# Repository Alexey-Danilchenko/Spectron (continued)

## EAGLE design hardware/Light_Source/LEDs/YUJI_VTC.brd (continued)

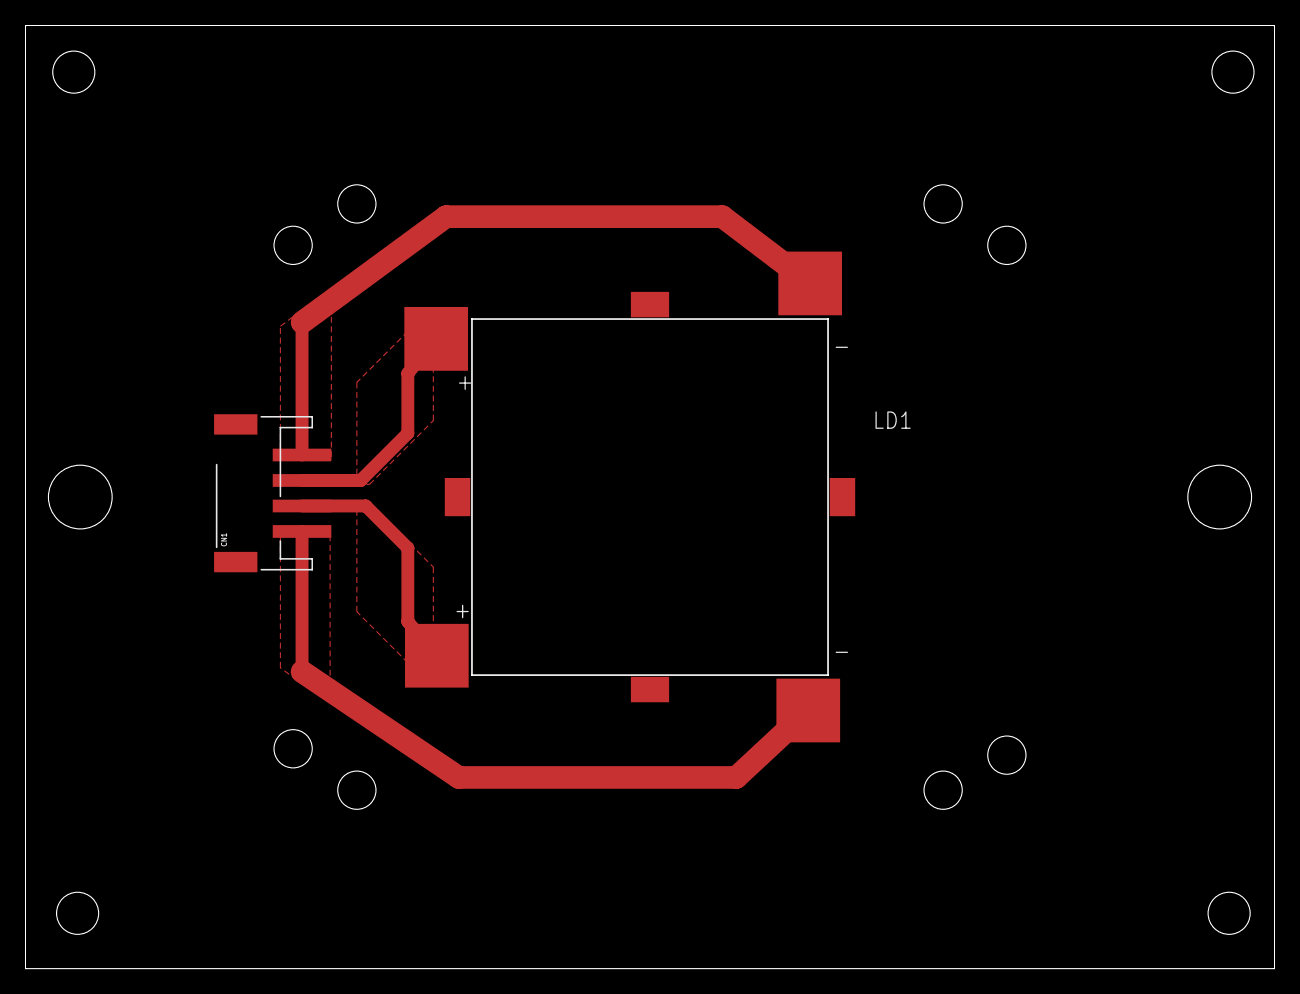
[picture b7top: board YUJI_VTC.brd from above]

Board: 2 copper layers, 98.0 x 74.0 mm, 6 parts (0 on the bottom side), 4 nets.

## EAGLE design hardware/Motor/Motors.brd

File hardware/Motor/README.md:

# Motor controller - programmable to scan of a range of wavelengths

This is the board that is responsible for monochromator automation. The board is capable of driving single stepper motor and receiving input from rotary encoder to help with position verification. The board requires minimum +12V DC power supply to operate. The board is also quite useful as standalone Particle Photon stepper driver.

Board schematic is also [available as standalone PDF](Motors.pdf). Bill of material [is available in Excel format](Motors_BOM.xlsx).

The following are the board layouts available (generated by OSH Park preview):

* Spectron 2 Motors - front and back

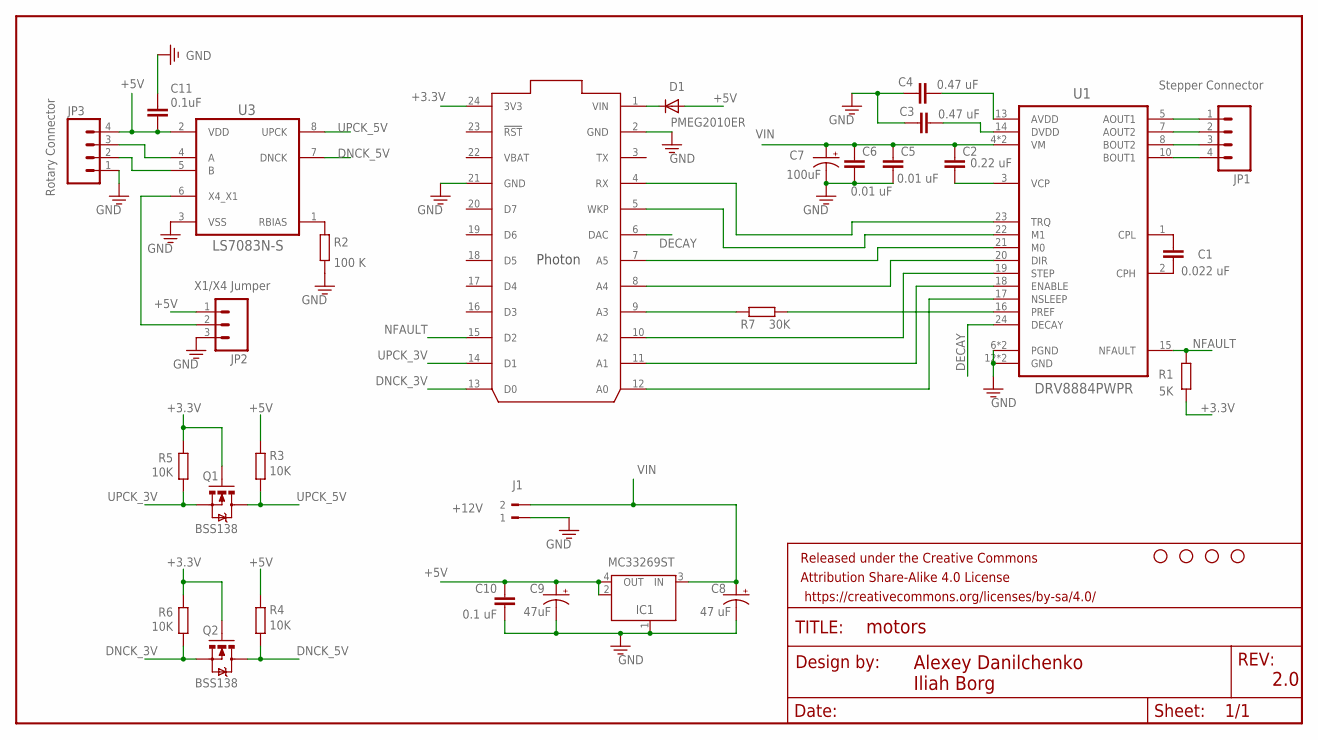
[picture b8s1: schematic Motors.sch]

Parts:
C1: 0.022 uF; C0805
C2: 0.22 uF; C0805
C3, C4: 0.47 uF; C0805
C5, C6: 0.01 uF; C0805
C7: 100uF; CT7343
C8: 47 uF; CT7343
C9: 47uF; CT7343
C10: 0.1 uF; C0805
C11: 0.1uF; C0805
D1: PMEG2010ER; SOD123
FRAME1: FRAME-LETTER; CREATIVE_COMMONS
IC1: MC33269ST; SOT223
J1: +12V; WEIDMULLER_PM5.08_2
JP1: Stepper Connector; 1X04
JP2: X1/X4 Jumper; 1X03
JP3: Rotary Connector; 1X04
Q1, Q2: BSS138; SOT23-3
R1: 5K; R0805
R2: 100 K; R0805
R3, R4, R5, R6: 10K; R0805
R7: 30K; R0805
STANDOFF1, STANDOFF2, STANDOFF3, STANDOFF4: STAND-OFF
U1: DRV8884PWPR; SOP65P640X120-29N
U2: PHOTON_WITH_HEADERS; PHOTON
U3: LS7083N-S; SOIC127P600X175-8N

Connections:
+3.3V: Q1.1 (G), Q2.1 (G), R1.1, R5.1, R6.1, U2.24 (3V3)
+5V: C9.+, C10.1, C11.2, D1.A, IC1.2 (OUT), IC1.4 (OUT), JP2.1, JP3.4, R3.1, R4.1, U3.2 (VDD)
DECAY: U1.24 (DECAY), U2.6 (DAC)
DNCK_3V: Q2.2 (S), R6.2, U2.13 (D0)
DNCK_5V: Q2.3 (D), R4.2, U3.7 (DNCK)
GND: C3.2, C4.2, C5.2, C6.2, C7.-, C8.-, C9.-, C10.2, C11.1, IC1.1 (GND/ADJ), J1.1, JP2.3, JP3.1, R2.2, U1.6 (PGND), U1.9 (PGND), U1.12 (GND), U1.25 (GND), U2.2 (GND), U2.21 (GND), U3.3 (VSS)
unnamed: U1.18 (ENABLE), U2.11 (A1)
unnamed: C2.2, U1.3 (VCP)
unnamed: C1.1, U1.2 (CPH)
unnamed: C1.2, U1.1 (CPL)
unnamed: U1.22 (M1), U2.5 (WKP)
unnamed: U1.17 (NSLEEP), U2.12 (A0)
unnamed: R7.1, U1.16 (PREF)
unnamed: C4.1, U1.13 (AVDD)
unnamed: C3.1, U1.14 (DVDD)
unnamed: D1.C, U2.1 (VIN)
unnamed: U1.19 (STEP), U2.10 (A2)
unnamed: U1.20 (DIR), U2.8 (A4)
unnamed: U1.21 (M0), U2.7 (A5)
unnamed: U1.23 (TRQ), U2.4 (RX)
unnamed: R7.2, U2.9 (A3)
unnamed: R2.1, U3.1 (RBIAS)
unnamed: JP1.1, U1.5 (AOUT1)
unnamed: JP1.2, U1.7 (AOUT2)
unnamed: JP2.2, U3.6 (X4_X1)
unnamed: JP1.3, U1.8 (BOUT2)
unnamed: JP1.4, U1.10 (BOUT1)
NFAULT: R1.2, U1.15 (NFAULT), U2.15 (D2)
ROTARY_A: JP3.3, U3.4 (A)
ROTARY_B: JP3.2, U3.5 (B)
UPCK_3V: Q1.2 (S), R5.2, U2.14 (D1)
UPCK_5V: Q1.3 (D), R3.2, U3.8 (UPCK)
VBAT: U2.22 (VBAT)
VIN: C2.1, C5.1, C6.1, C7.+, C8.+, IC1.3 (IN), J1.2, U1.4 (VM), U1.11 (VM)

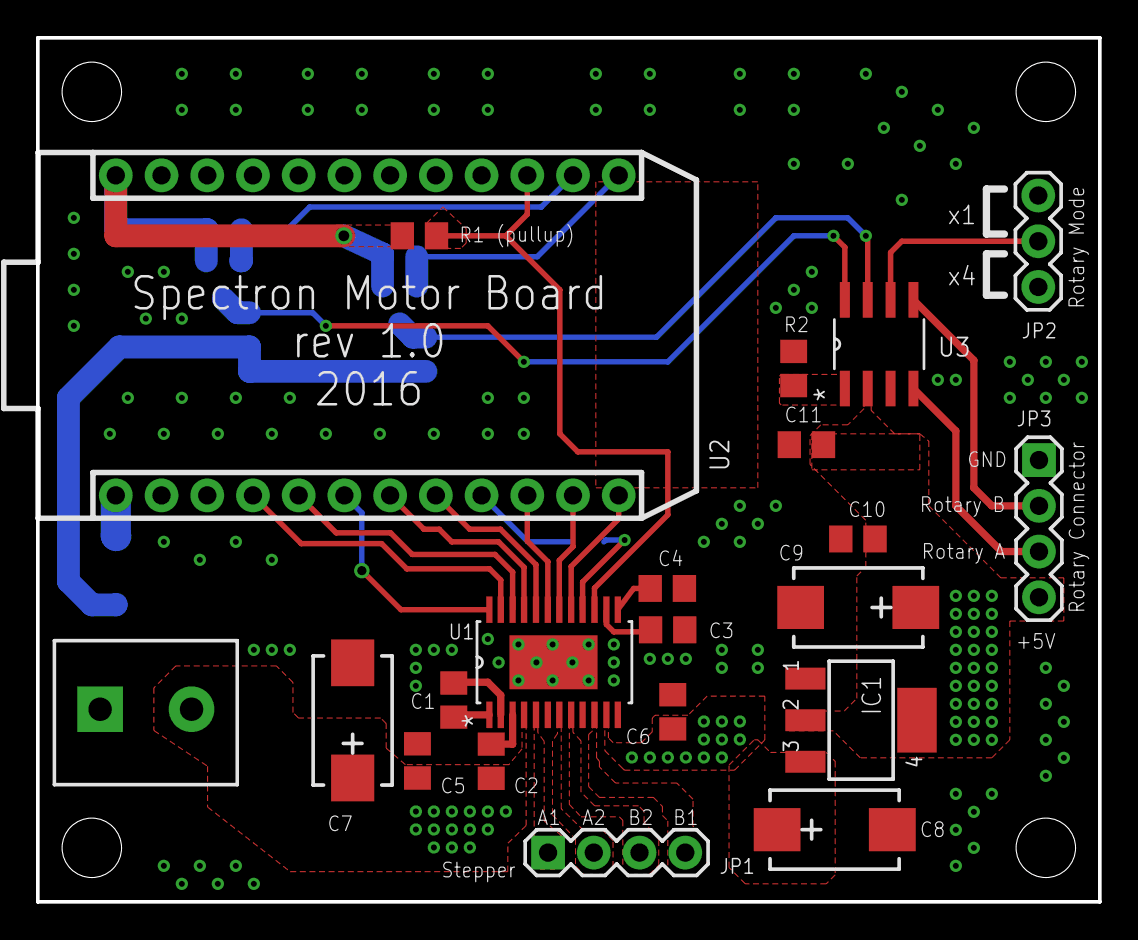
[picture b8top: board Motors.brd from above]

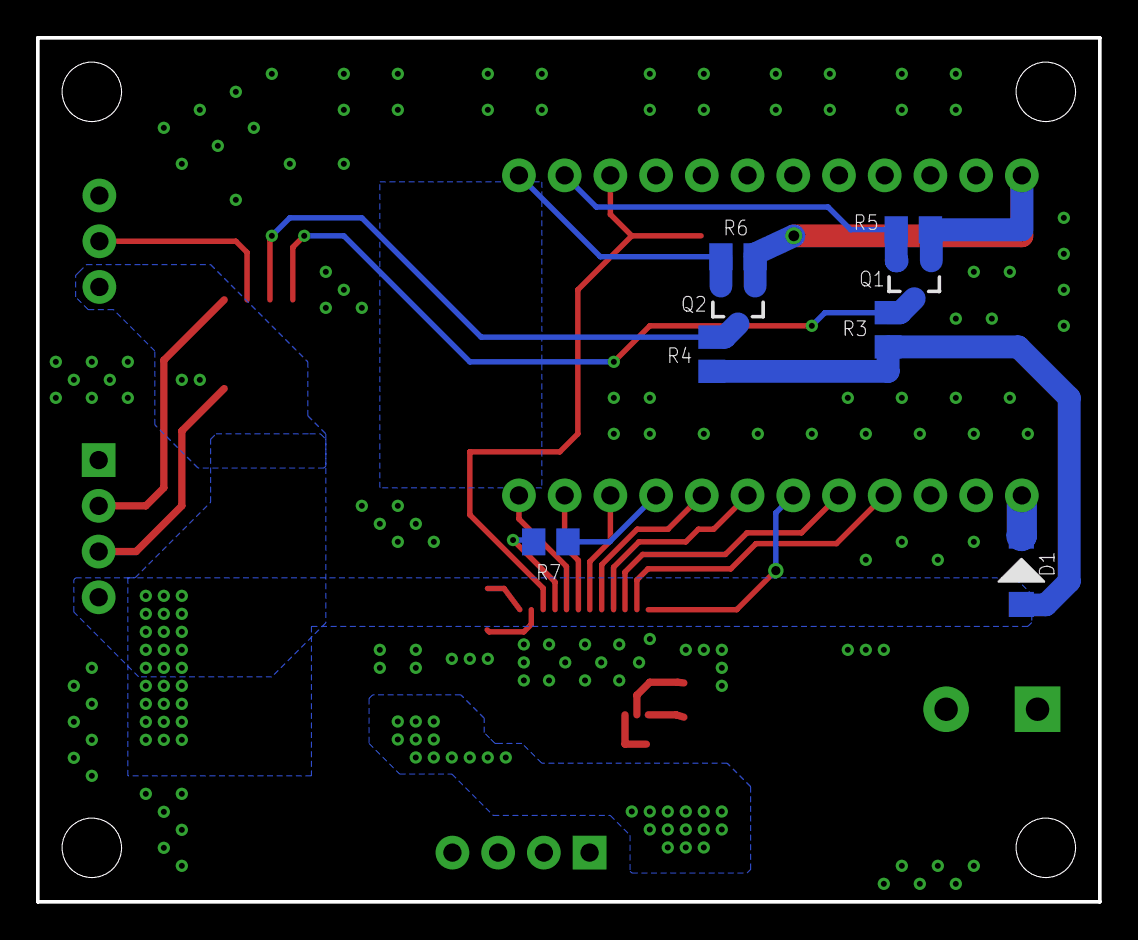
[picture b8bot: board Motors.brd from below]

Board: 2 copper layers, 59.0 x 48.0 mm, 34 parts (8 on the bottom side), 33 nets.

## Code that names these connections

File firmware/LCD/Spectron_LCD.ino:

/*
 *  Spectron_LCD.ino - Demo application of the Spectron board capabilities  
 *                     with Adafruit ILI9340 TFT screen displaying measured 
 *                     spectrum. This is not actively maintained.
 *
 *  Copyright 2015-2017 Alexey Danilchenko
 *
 *  This program is free software; you can redistribute it and/or modify
 *  it under the terms of the GNU General Public License as published by
 *  the Free Software Foundation; either version 3, or (at your option)
 *  any later version with ADDITION (see below).
 *
 *  This program is distributed in the hope that it will be useful,
 *  but WITHOUT ANY WARRANTY; without even the implied warranty of
 *  MERCHANTABILITY or FITNESS FOR A PARTICULAR PURPOSE.  See the
 *  GNU General Public License for more details.

 *  You should have received a copy of the GNU General Public License
 *  along with this program; if not, write to the Free Software
 *  Foundation, 51 Franklin Street - Fifth Floor, Boston,
 *  MA 02110-1301, USA.
 */

SYSTEM_MODE(MANUAL);

#include "C12666MA.h"
#include "Adafruit_ILI9340.h"

#define ADC_REF_SEL_1  A1
#define ADC_REF_SEL_2  A0
#define ADC_CNV        DAC
#define SPI_SS_1       WKP
#define D_PWM          RX
#define SPI_SS_2       A2
#define SPI_MOSI       A5
#define SPI_MISO       A4
#define SPI_SCK        A3
#define SDA            D0
#define SCL            D1

#define TRG_IN         A2   // extrenal trigger button
#define TRG_FLASH      TX
#define TRG_CAMERA     D2

#define TRG_3V         D3
#define EOS_3V         D4
#define CLK_3V         D5
#define ST_3V          D6
#define GAIN_3V        D7

#define LCD_DC        SDA
#define LCD_RESET     SCL
#define LCD_SD_CS     SPI_SS_2
#define LCD_CS        SPI_SS_1
#define LCD_MOSI      SPI_MOSI
#define LCD_MISO      SPI_MISO
#define LCD_SCK       SPI_SCK
#define LCD_BACKLIGHT D_PWM

#define INACTIVE_DELAY_MS 120000

// calibration data for my sensor 15F00163
const float CALIBRATION_15F00163[] =
    {323.3668711, 2.384682045, -5.995865297E-4, -8.602293347E-6, 1.840343099E-8, -1.424592223E-11};

// spectrometer object - can be only one per application
C12666MA spec(TRG_3V,
              EOS_3V,
              GAIN_3V,
              CLK_3V,
              ST_3V,
              TRG_CAMERA,
              ADC_REF_SEL_1,
              ADC_REF_SEL_2,
              ADC_CNV,
              CALIBRATION_15F00163);

// TFT screen object
Adafruit_ILI9340 tft(LCD_SD_CS,
                     LCD_DC,
                     LCD_RESET);

// Wavelength indexes for screen 400,450,500,550,600,650,700,750
#define WV_LABELS      10
#define WV_LABEL_START 350
#define WV_LABEL_STEP  50
uint16_t wvLabelIndex[WV_LABELS];

// indicator if black was measured
bool blackMeasured = true;

// last active time
unsigned long lastActive = 0;

// draw the main screen
void drawScreen()
{
    tft.3Init();
    tft.fillScreen(ILI9340_BLACK);
    tft.setRotation(3);    // orientation landscape

    // draw header
    tft.setCursor(0, 0);
    tft.setTextColor(ILI9340_WHITE);
    tft.setTextSize(1);
    tft.print("Peak: ");
    tft.print(spec.getPeakWavelength(), 2);
    tft.print("nm    Max: ");
    tft.print(spec.getPeakValue());
    tft.print("    Black: ");
    tft.print(spec.getMaxBlack());

    // draw axis
    uint16_t g_x = 0, g_y = 10, g_w = 320, g_h = 220;
    uint16_t color = ILI9340_WHITE;
    tft.drawFastHLine(0, g_y+g_h, g_w, color);
    uint16_t lblWavelength = WV_LABEL_START;
    for (int i=0; i<WV_LABELS; i++)
    {
        if (wvLabelIndex[i] == SPEC_PIXELS)
            break;
        uint16_t l_x = g_x + (wvLabelIndex[i] * g_w / SPEC_PIXELS);
        tft.drawFastVLine(l_x, g_y+g_h-1, 3, color);
        tft.setCursor(l_x - 8, g_y+g_h+2);
        tft.print(lblWavelength);
        lblWavelength += WV_LABEL_STEP;
    }

    // draw the maxvoltage
    // draw spectrum
    if (spec.hasMeasuredData())
    {
        uint16_t x0 = g_x;
        uint16_t y0 = g_y + g_h - (((uint32_t)g_h*spec.getMeasurement(0) + 16383) /16384);
        for (int i=1; i<SPEC_PIXELS; i++)
        {
            uint16_t x1 = g_x + ((i * g_w + SPEC_PIXELS - 1) / SPEC_PIXELS);
            uint16_t y1 = g_y + g_h - (((uint32_t)g_h*spec.getMeasurement(i) + 16383) /16384);
            tft.drawLine(x0, y0, x1, y1, ILI9340_YELLOW);
            x0 = x1;
            y0 = y1;
        }
    }
    else if (!blackMeasured)
    {
        tft.setTextSize(2);
        tft.setCursor(g_x, g_y + (g_h>>1)- 32);
        tft.setTextColor(ILI9340_RED);
        tft.println("    Cover the sensor and");
        tft.println("  trigger black reference");
        tft.println("       measurement");
    }
}

// main firmware initialisation
void setup()
{
    pinMode(LCD_BACKLIGHT, OUTPUT);
    pinMode(LCD_CS,        OUTPUT);
    pinMode(LCD_SD_CS,     OUTPUT);
    pinMode(LCD_DC,        OUTPUT);
    pinMode(LCD_RESET,     OUTPUT);

    pinMode(TRG_IN,     INPUT_PULLUP);
    pinMode(TRG_CAMERA, OUTPUT);
    pinMode(TRG_FLASH,  OUTPUT);

    // reset everything
    pinResetFast(LCD_CS);
    pinResetFast(LCD_SD_CS);
    pinResetFast(LCD_DC);
    pinResetFast(LCD_RESET);


    // initialise spectrometer
    spec.begin();
    spec.setIntTime(500);   // 0.5s to start with
    spec.setAdcReference(ADC_4V);

    // get the wavelength label indexes
    uint16_t idx = 0;
    for (int i=0; i<WV_LABELS; i++)
    {
        uint16_t lblWavelength = WV_LABEL_START + (i * WV_LABEL_STEP);
        while (idx < SPEC_PIXELS &&
               lblWavelength > spec.getWavelength(idx))
               ++idx;
        if (idx < SPEC_PIXELS)
            wvLabelIndex[i] = idx;
        else
            wvLabelIndex[i] = SPEC_PIXELS;
    }

    // enable TFT backlight
    pinSetFast(LCD_BACKLIGHT);
    tft.begin();

    // paint the screen
    drawScreen();

    lastActive = millis();
}

// Main event loop:
//     - Wait for trigger button press
//     - Start spectometer measurement and trigger camera/flash
//     - Display the results on TFT
//     - Store results on SD card
void loop(void)
{
    // poll the trigger button
    if (pinReadFast(TRG_IN) == LOW)
    {
        // debounce check
        delay(100);
        if (pinReadFast(TRG_IN) == LOW)
        {
            pinSetFast(LCD_BACKLIGHT);
            lastActive = millis();
            
            // initiate measurement
            spec.takeMeasurement();

            // paint the screen
            drawScreen();
        }
    }

    // check for inactivity
    if ((millis() - lastActive) > INACTIVE_DELAY_MS)
        pinResetFast(LCD_BACKLIGHT);

    // call for Spark process for manual system mode
    if (Particle.connected())
        Particle.process();
    else
        Particle.connect();
 }

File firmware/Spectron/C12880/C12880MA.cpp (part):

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#define SPEC_PIXELS  288

// standard SPI pins
#define SPI_MOSI    A5
#define SPI_MISO    A4
#define SPI_SCK     A3

//
// State flow with single read integration cycle:
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#define ST_LEAD_TICKS        7            // ticks after ST goes high (on falling CLK) when integration really starts
#define READ_TICKS           ((87 + SPEC_PIXELS)*TICKS_PER_PIXEL)
#define TRG_CYCLES           (SPEC_PIXELS + 88)     // spec pixels + 88 cycles after ST goes low
#define EXT_TRG_HIGH_TICKS   uSecToTicks(1000)      // duration of ext TRG pin high signal - 1mSec

// Integration ticks - change as needed
static uint32_t INTEG_TICKS = MIN_INTEG_TIME_TICKS;
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static uint32_t              specCounter = 0;          // tick counter
static uint32_t              specCLK = 0;              // current clock pin state
static uint32_t              specST = 0;               // current ST pin state
static volatile uint32_t     extTrigger = 0;           // current trigger pin state
static volatile uint32_t     specTRGCounter = 0;       // spec TRG cycles counter
static volatile uint32_t     extTRGCounter = 0;        // ext TRG cycles counter
static volatile uint16_t     specReadCycleCounter = 0; // reading cycles counter
static uint32_t*             specData = 0;             // pointer to current data for ADC reads
static uint16_t*             specDataCounter = 0;      // pointer to current data for ADC reads counter
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#define CR1_CLEAR_MASK   ((uint16_t)0x3040)

// initialise ADC (AD7980) and setup SPI
inline void startADC(uint8_t adc_cnv_pin)
{
    // disable whatever else might have SPI enabled via HAL
    SPI.end();
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    HAL_Pin_Mode(MOSI, AF_OUTPUT_PUSHPULL);

    // Ensure that there is no glitch on SS pin
    PIN_MAP[adc_cnv_pin].gpio_peripheral->BSRRL = PIN_MAP[adc_cnv_pin].gpio_pin;
    HAL_Pin_Mode(adc_cnv_pin, OUTPUT);

    // Get the SPIx CR1 value */
    uint16_t tmpreg = SPI_BASE->CR1;
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
// Function to perform reading ADC7980.
// This does up to two accumulated reads of the ADC
// where the state of the TRG pin is checked following
// the second ADC conversion completion
inline void readADC(uint32_t* data, uint16_t* dataCounts)
{
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// --------------------------------------------------
//   Timer and spectrometer clock handling routines
// --------------------------------------------------
// TRG pin handling interrupt
void spectroTRGInterrupt(void)
{
    if ((EXTI->PR & specPinTRG) && (EXTI->IMR & specPinTRG))
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    TIM_ITConfig(TIM7, TIM_IT_Update, ENABLE);
    TIM_Cmd(TIM7, ENABLE);

    // setup spec TRG pin interrupts
    uint8_t trgPortNumber = 0;  // port A by default

    // clear pending EXTI interrupt flag for the TRG pin
    EXTI->PR = specPinTRG;

    // set the port number
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    else if (specPinTRG_Info->gpio_peripheral == GPIOD)
        trgPortNumber = 3;

    // connect EXTI Line to TRG pin
    SYSCFG_EXTILineConfig(trgPortNumber, specPinTRG_Info->gpio_pin_source);

    // enable TRG pin interrupt
    EXTI->IMR  |= specPinTRG;    // enable interrupt
    EXTI->RTSR |= specPinTRG;    // set raising edge

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    // disable timer peripheral
    TIM_DeInit(TIM7);

    // disable TRG pin interrupts
    EXTI->PR = specPinTRG;       // clear pending
    EXTI->IMR  &= ~specPinTRG;   // mask interrupt
    EXTI->RTSR &= ~specPinTRG;   // clear raising edge

    // disable NVIC IRQ line if it is not shared
    if (sysIrqHandler == 0)
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
    // Setup pins
    pinMode(adc_cnv_,  OUTPUT);
    pinMode(SPI_MOSI,  OUTPUT);
    pinMode(SPI_MISO,  INPUT);
    pinMode(SPI_SCK,   OUTPUT);
    pinMode(spec_eos_, INPUT);
    pinMode(spec_trg_, INPUT);
    pinMode(spec_st_,  OUTPUT);
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
    // reset everything
    pinResetFast(adc_cnv_);
    pinResetFast(SPI_MOSI);
    pinResetFast(SPI_SCK);
    pinResetFast(spec_st_);
    pinResetFast(spec_clk_);
    if (ext_trg_ != NO_PIN)
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    if (ext_trg_ls_ != NO_PIN)
        pinResetFast(ext_trg_ls_);

    // Attach update interrupt for TIM7 and TRG pin
    // HAL version of this would be
    //   attachSystemInterrupt(SysInterrupt_TIM7_IRQ, spectroClockInterrupt);
    //   attachInterrupt(spec_trg_, spectroTRGInterrupt, RAISING, 1);
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    int is = __get_PRIMASK();
	__disable_irq();

    // store the system interrupt if TRG pin ISR is shared across several pins
    if (GPIO_IRQn[trgPinSource] == EXTI9_5_IRQn ||
        GPIO_IRQn[trgPinSource] == EXTI15_10_IRQn)
        sysIrqHandler = (EXT_IRQ_Handler)isrs[trgISRIndex];

    // override TIM7 and TRG pin interrupts
    isrs[TIM7Index]   = (uint32_t)spectroClockInterrupt;
    isrs[trgISRIndex] = (uint32_t)spectroTRGInterrupt;

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        dataCounts[i] = 0;
    }

    // initialise light trigger pin if triggering is enabled
    if (ext_trg_ls_ != NO_PIN && doLightTriggering)
    {
        STM32_Pin_Info* PIN_MAP = HAL_Pin_Map();
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
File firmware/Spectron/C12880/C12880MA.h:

/*
 *  C12880MA.h - Hamamatsu C12880MA driver for Spectron board.
 *
 *  Copyright 2017-2020 Alexey Danilchenko, Iliah Borg
 *
 *  This program is free software; you can redistribute it and/or modify
 *  it under the terms of the GNU General Public License as published by
 *  the Free Software Foundation; either version 3, or (at your option)
 *  any later version with ADDITION (see below).
 *
 *  This program is distributed in the hope that it will be useful,
 *  but WITHOUT ANY WARRANTY; without even the implied warranty of
 *  MERCHANTABILITY or FITNESS FOR A PARTICULAR PURPOSE.  See the
 *  GNU General Public License for more details.

 *  You should have received a copy of the GNU General Public License
 *  along with this program; if not, write to the Free Software
 *  Foundation, 51 Franklin Street - Fifth Floor, Boston,
 *  MA 02110-1301, USA.
 */

#if !defined(_C12880MA_H_)
#define _C12880MA_H_

#include "application.h"
#include "Spectrometer.h"

// Spectrometer class
//
// This class uses TIM7 timer interrupt as well as SPI so it affects their
// configuration when used
//
class C12880MA: public CSpectrometer  {
private:
    // pin definitions - ADC assumes use of the standard SPI pins
    uint8_t adc_cnv_, spec_eos_, spec_trg_, spec_clk_, spec_st_, ext_trg_, ext_trg_ls_;

protected:
    // --------------------------------------------------------------------------
    //  Virtual methods - hardware specific implementations for Hamamatsu C12880
    // --------------------------------------------------------------------------

    // This is the main method that should be overriden by specific spectrometer
    // implementation. It should implement hardware specific initialisation, reading 
    // loop and termination.
    void readSpectrometer(double measTimeUs, 
                          bool doExtTriggering, 
                          bool doLightTriggering) override;

    // Hardware specific sensor constraints - sets data variable for a specific sensor
    // constraint (pointer is expected to point to a variable of correct datatype for 
    // that constraint)
    bool getSensorConstraint(sensor_constraint_t sensConstraint, void* data) override;

    // Hardware specific sets integration time in microseconds for a single
    // measurement cycle.
    //
    // NOTE: if not within sensor allowed boundaries then it will be set to
    //       closest minimum or maximum allowed value
    // NOTE: internally time is measured in clock cycles so real integration
    //       time will be aligned to the clock cycle boundaries
    void setIntTimeInternal(double timeUs, bool saveState = false) override;

    // Hardware specific sets the external trigger to measurement delay time.
    // This defines time interval in uSec that offsets external trigger from 
    // the measurement. I.e. external trigger is raised and after this delay 
    // the integration and measurement starts.
    //
    // Specifying -1 as  delay will disable the external trigger
    void setExtTrgMeasDelayInternal(double delayUs, bool saveState = false) override;

public:

    // Constructor/destructor
    // Parameters:
    //     spec_eos      - C12880MA EOS receving pin
    //     spec_trg      - C12880MA TRG controlling pin
    //     spec_clk      - C12880MA CLK clock pin
    //     spec_st       - C12880MA ST start pin
    //     adc_ref_sel1  - ADC voltage reference selection pin 1
    //     adc_ref_sel2  - ADC voltage reference selection pin 2
    //     adc_cnv       - ADC conversion pin (essentially SPI selection pin for ADC SPI intreface)
    //     ext_trg       - optional trigger pin for capture device (setting HIGH triggers external device)
    //     ext_trg_ls    - optional trigger pin for lightsource (setting HIGH triggers light source)
    //     wvCalibration - factory wavelength calibration factors (array of 6 doubles from Hamamatsu test sheet)
    //     baseEEPROM    - base address to srore the spectrometer settings in EEPROM (-1 if not used)
    C12880MA(uint8_t spec_eos, uint8_t spec_trg, uint8_t spec_clk, uint8_t spec_st,
             uint8_t adc_ref_sel1, uint8_t adc_ref_sel2, uint8_t adc_cnv,
             uint8_t ext_trg, uint8_t ext_trg_ls, 
             const double *wvCalibration, const int baseEEPROM = 0);
    ~C12880MA();

    // Initialise known pins. Specific hardware implementations typically will
    // have their own implementations of this initialising spectrometer specific
    // pins.
    bool begin();

    // --------------------------------------------------------------------------
    //  Virtual methods - hardware specific implementations for Hamamatsu C12666
    // --------------------------------------------------------------------------

    // Return trigger measurement delay in specified units
    double getExtTrgMeasDelay(time_units_t units = T_USEC) override;
    
    // Return integration time in specified units
    double getIntTime(time_units_t units = T_USEC) override;
};

#endif

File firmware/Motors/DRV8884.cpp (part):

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//
#define  TIMER_PRESCALER     599       // for basic timers at 60MHz it gives 10us timer unit counter
#define  TIMER_UNITS_PER_SEC 100000UL  // number of timer units per sec for the above prescaler
#define  MIN_TIMER_PERIOD    10        // min timer tick - in above 10us units it will trigger every 0.1ms
#define  MAX_TIMER_PERIOD    50000     // max timer tick - in above 10us units it will trigger every 500ms
uint32_t TIMER_PERIOD_CNT =  1000;     // in above 10us units it will trigger every 10ms

// State machine
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#endif
                 )
{
    pinNfault_  = nfault;
    pinDecay_   = decay;
    pinTRQ_     = trq;
    pinM0_      = m0;
    pinM1_      = m1;
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
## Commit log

2017-04-17 Initial submisssion
    Submission of well tested hardware, firmware. Software is being developed and will follow later.
2018-07-03 Cumulative changes: adding light sources, boards, firmwares, construction details
2018-09-26 Updated Xenon light source and descriptions.
2018-12-01 Spectrometer firmwares and sample application for Windows
    Spectrometer firmwares rewritten to provide automatic measurements, calibration and afew other features. Sample Windows application is provided to operate Spectron spectrometer board and measure spec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
2018-12-01 Readme fixes
2018-12-02 Bugfixes for C12880 and application
2019-04-13 Update 1.2
    Firmware changes:
    - configurable spectral range
    - saturation and black level calibration
    - spectral response calibration and normalisation of measurements
    SpectrometerApp changes:
    - Spectrometer calibration page allowing calibration of various spectrometer properties
2019-04-15 Minor fixes
    Fixed copy operator that prevented re-login to other devices
2021-12-15 Added Camera SRF application note
2021-12-15 Small formatting corrections
2021-12-15 More formatting
2021-12-15 Last formatting fixes
2023-01-18 Updated links
2025-01-26 Restructuring of the project. Linearisation code, bias calculations etc - work in progress
